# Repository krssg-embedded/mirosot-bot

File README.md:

# mirosot-bot
Board schematics, designs, layout. CAD files and relevant documentation regarding mirosot bots used in Code-O-Soccer Event

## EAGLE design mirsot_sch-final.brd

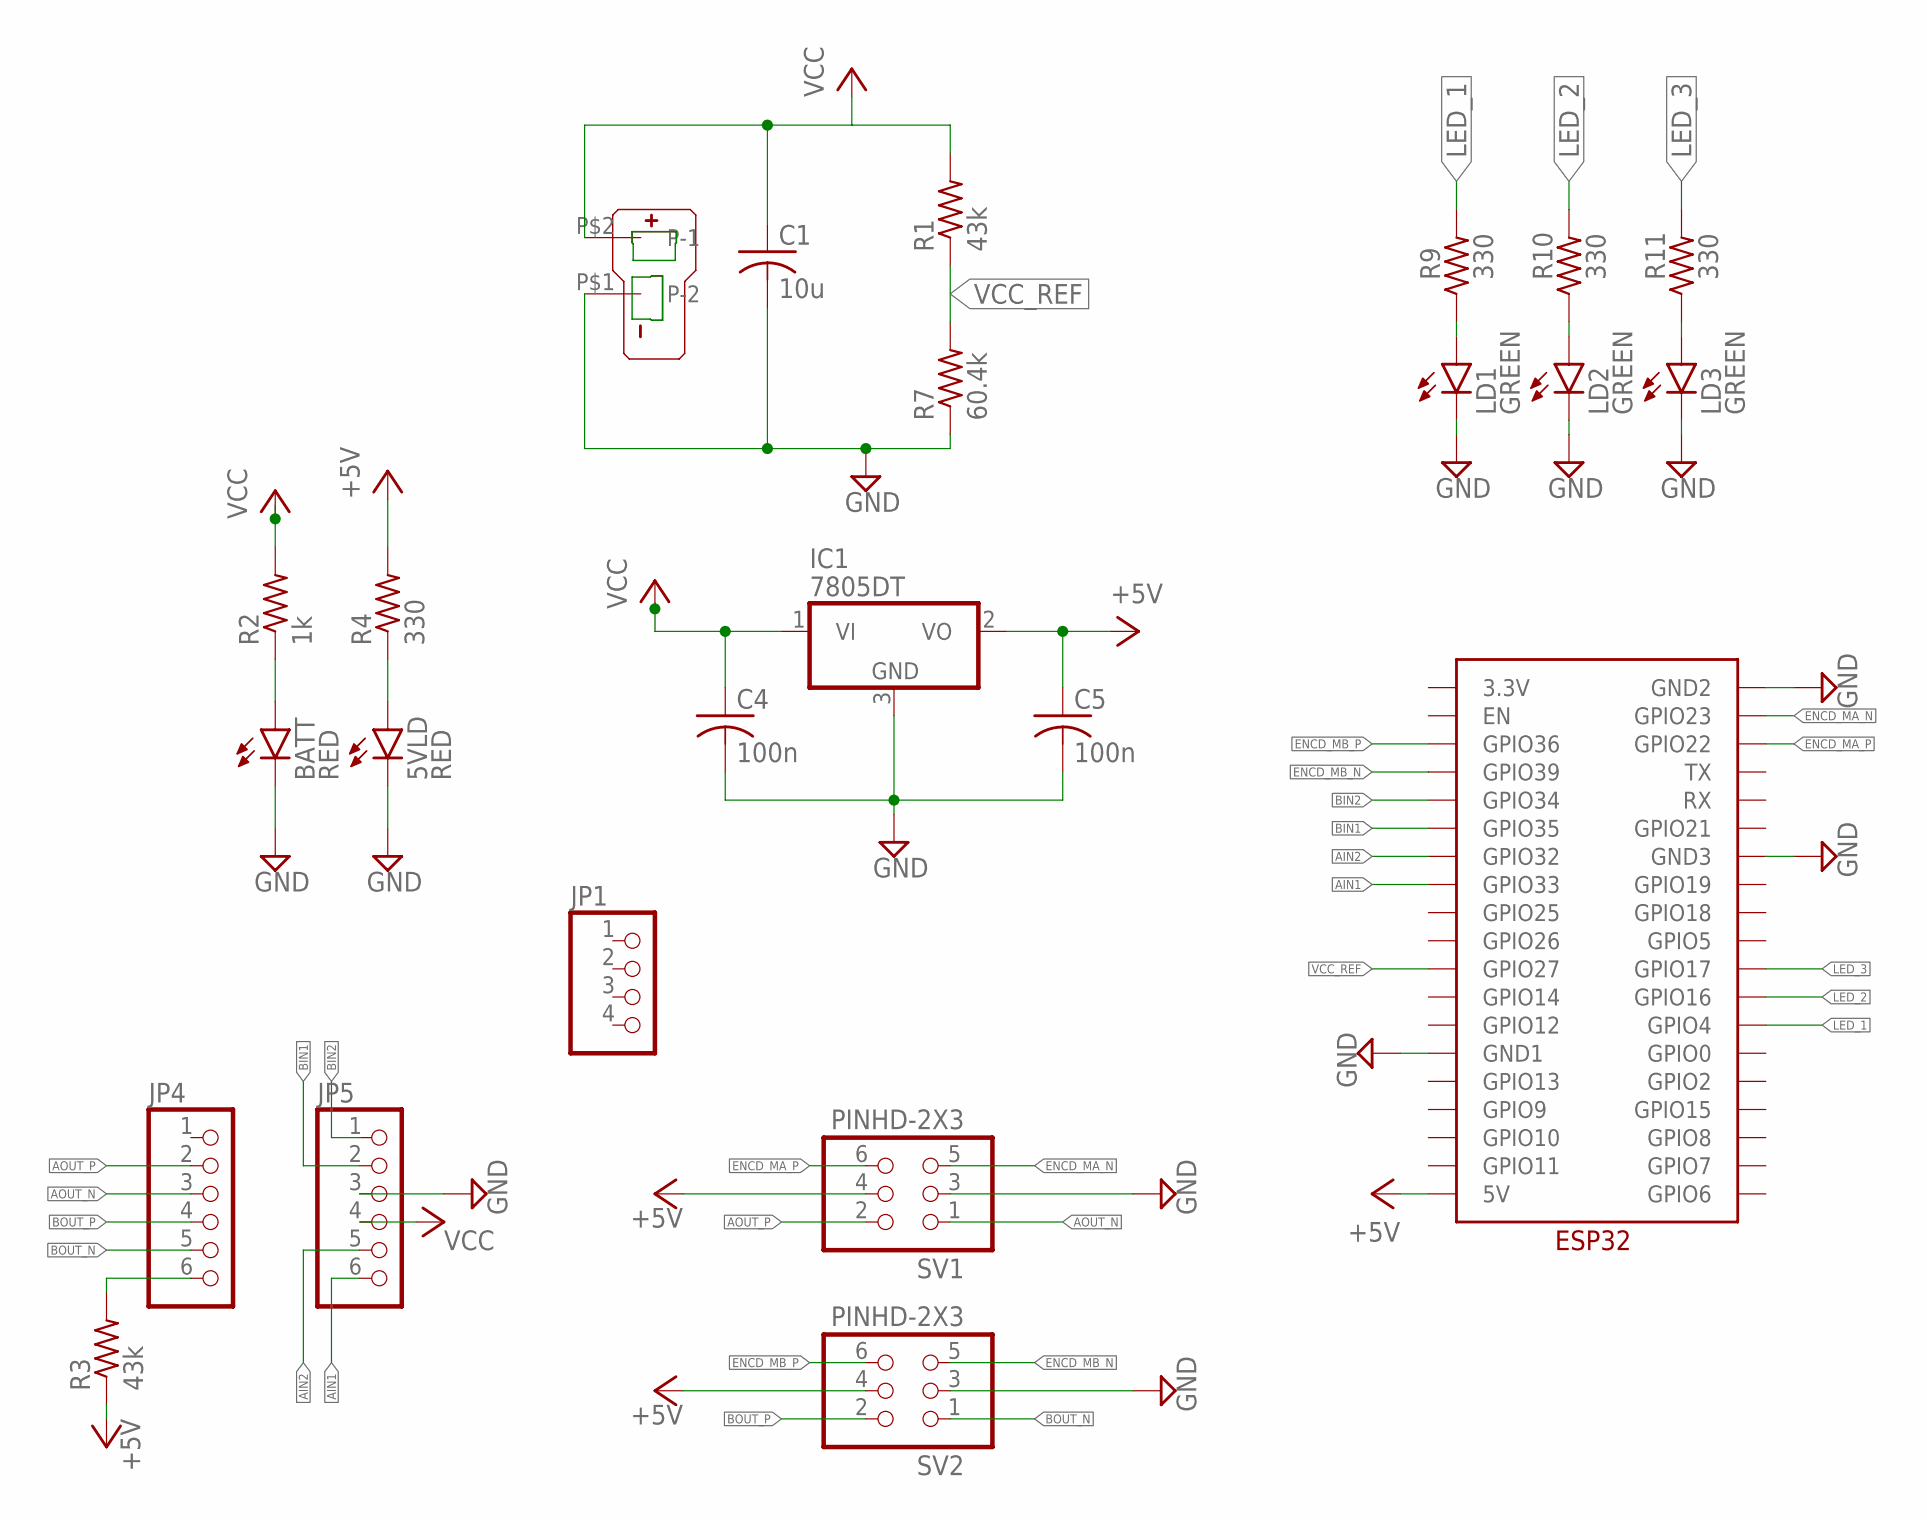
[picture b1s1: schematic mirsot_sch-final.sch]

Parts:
5VLD: RED; SML1206
BATT: RED; SML1206
C1: 10u; C1206K
C4, C5: 100n; C0603K
IC1: 7805DT; TO252
JP1: PINHD-1X4; 1X04
JP4, JP5: PINHD-1X6; 1X06
LD1, LD2, LD3: GREEN; SML1206
R1, R3: 43k; M1206
R2: 1k; M1206
R4, R9, R10, R11: 330; M1206
R7: 60.4k; M1206
SV1, SV2: PINHD-2X3; 2X03
U$1: T_PLUG_CONNECTOR_H
U$2: ESP32

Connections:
+5V: C5.1, IC1.2 (VO), R3.1, R4.2, SV1.4, SV2.4, U$2.5V
AIN1: JP5.6, U$2.GPIO33
AIN2: JP5.5, U$2.GPIO32
AOUT_N: JP4.3, SV1.1
AOUT_P: JP4.2, SV1.2
BIN1: JP5.2, U$2.GPIO35
BIN2: JP5.1, U$2.GPIO34
BOUT_N: JP4.5, SV2.1
BOUT_P: JP4.4, SV2.2
ENCD_MA_N: SV1.5, U$2.GPIO23
ENCD_MA_P: SV1.6, U$2.GPIO22
ENCD_MB_N: SV2.5, U$2.GPIO39
ENCD_MB_P: SV2.6, U$2.GPIO36
GND: 5VLD.C, BATT.C, C1.2, C4.2, C5.2, IC1.3 (GND), JP5.3, LD1.C, LD2.C, LD3.C, R7.1, SV1.3, SV2.3, U$1.P$1 (P-2), U$2.GND1, U$2.GND2, U$2.GND3
LED_1: R9.2, U$2.GPIO4
LED_2: R10.2, U$2.GPIO16
LED_3: R11.2, U$2.GPIO17
unnamed: JP4.6, R3.2
unnamed: BATT.A, R2.1
unnamed: LD1.A, R9.1
unnamed: LD2.A, R10.1
unnamed: 5VLD.A, R4.1
unnamed: LD3.A, R11.1
VCC: C1.1, C4.1, IC1.1 (VI), JP5.4, R1.2, R2.2, U$1.P$2 (P-1)
VCC_REF: R1.1, R7.2, U$2.GPIO27

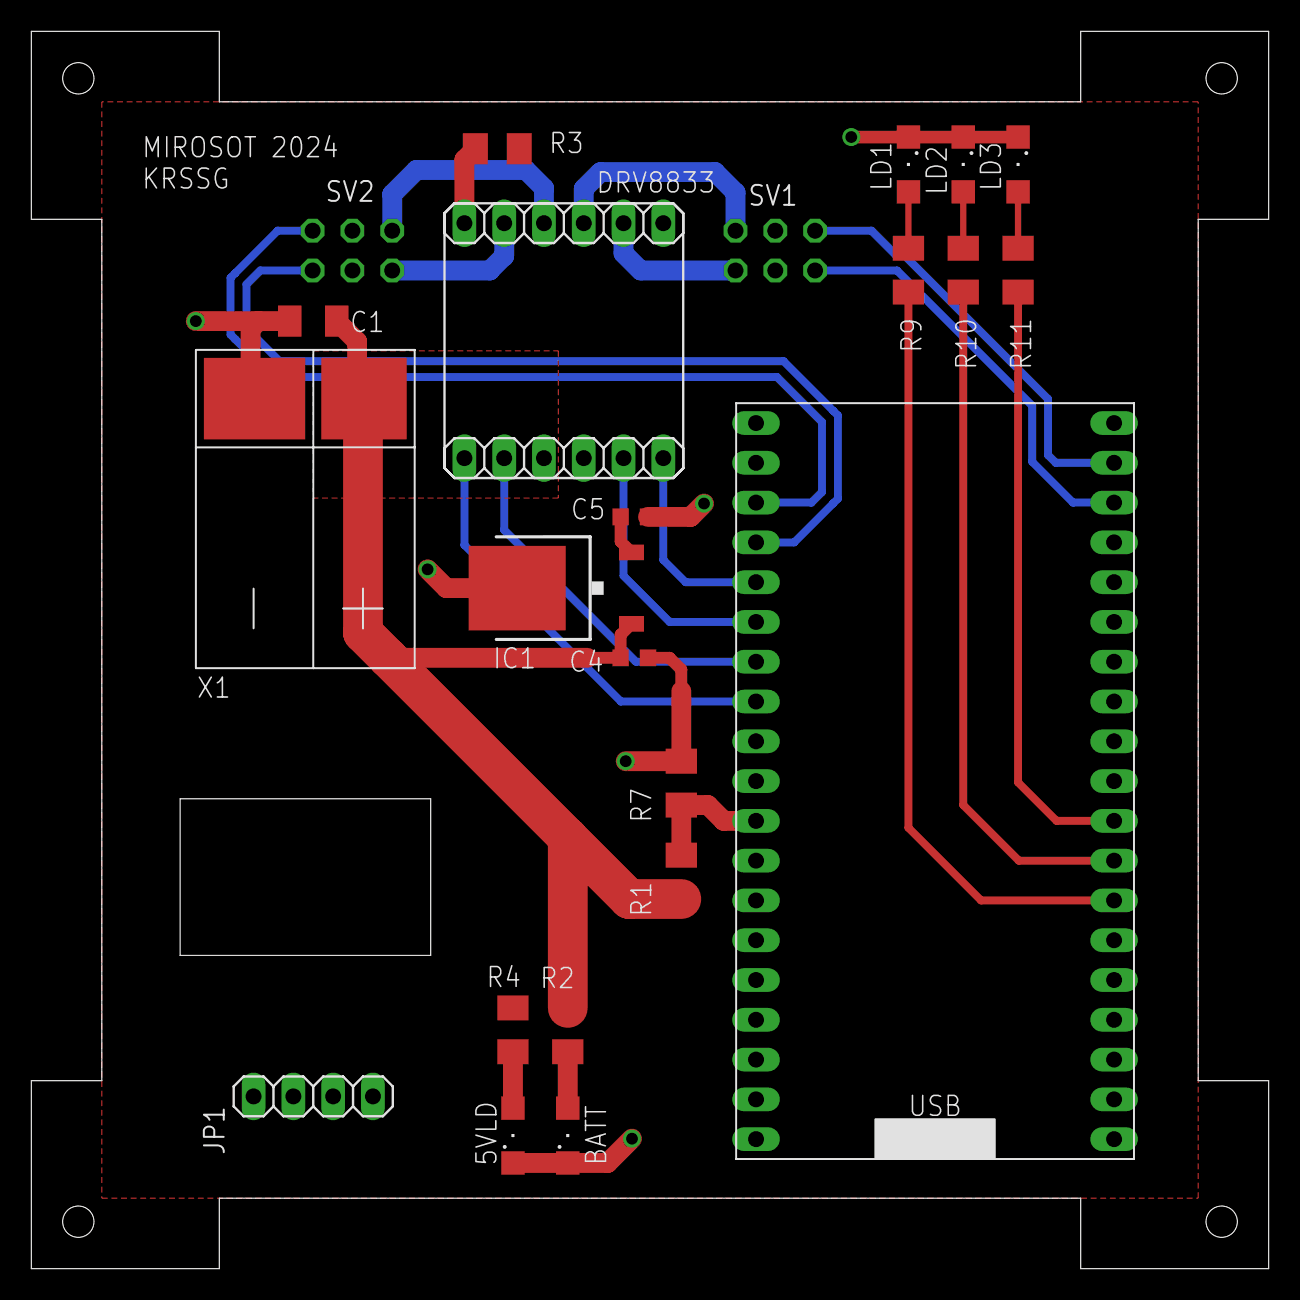
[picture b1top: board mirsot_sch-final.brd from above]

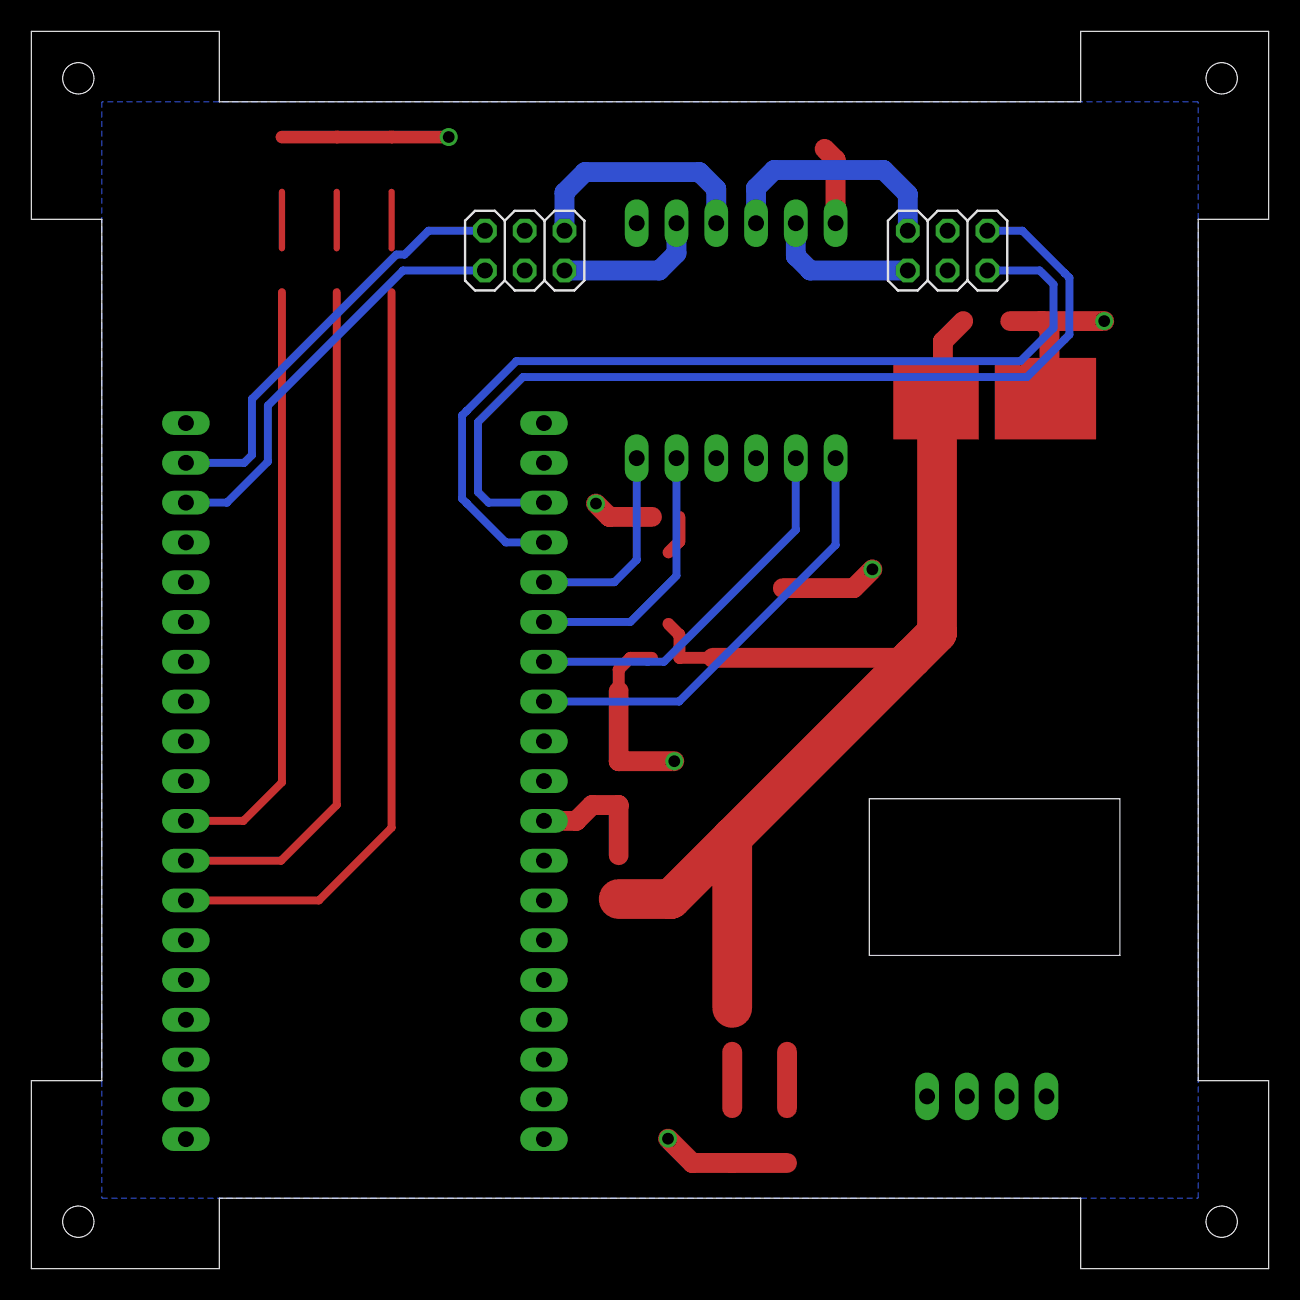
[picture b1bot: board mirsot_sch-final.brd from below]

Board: 2 copper layers, 79.0 x 79.0 mm, 24 parts (2 on the bottom side), 25 nets.

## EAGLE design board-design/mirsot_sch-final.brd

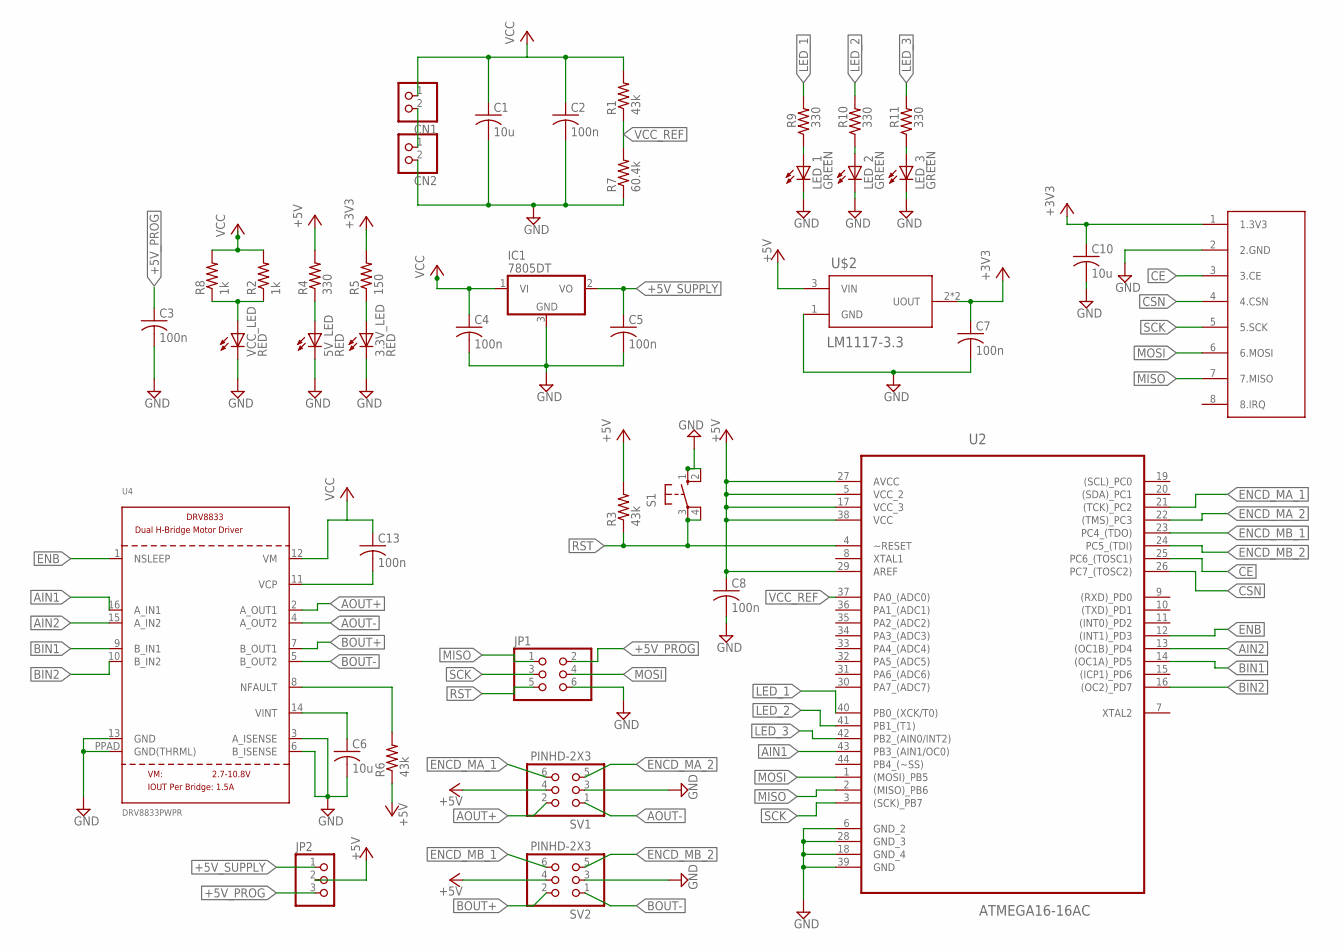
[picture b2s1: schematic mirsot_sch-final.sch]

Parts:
3.3V_LED, 5V_LED: RED; CHIPLED_0603
C1, C6, C10: 10u; C0603
C2, C3, C4, C5, C7, C8, C13: 100n; C0603
CN1, CN2: JST_2PIN-THM; JST-PH-2-THM
IC1: 7805DT; TO252
JP1: PINHD-2X3; 2X03
JP2: PINHD-1X3; 1X03
LED_1, LED_2, LED_3: GREEN; CHIPLED_0603
R1, R3, R6: 43k; R1206
R2, R8: 1k; R1206
R4, R9, R10, R11: 330; R1206
R5: 150; R2512
R7: 60.4k; R1206
S1: 10-XX; B3F-10XX
SV1, SV2: PINHD-2X3; 2X03
U2: ATMEGA16-16AC; QFP80P1200X1200X120-44N
U4: DRV8833PWPR; HTSSOP16
U$1: NRF24L01+
U$2: LM1117-3.3; SOT-223
VCC_LED: RED; CHIPLED_0603

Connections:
+3V3: C7.1, C10.1, R5.2, U$1.1 (1.3V3), U$2.2 (UOUT), U$2.4 (UOUT)
+5V: C8.1, JP2.2, R3.2, R4.2, R6.1, SV1.4, SV2.4, U2.5 (VCC_2), U2.17 (VCC_3), U2.27 (AVCC), U2.29 (AREF), U2.38 (VCC), U$2.3 (VIN)
+5V_PROG: C3.1, JP1.2, JP2.3
+5V_SUPPLY: C5.1, IC1.2 (VO), JP2.1
AIN1: U2.43 (PB3_(AIN1/OC0)), U4.16 (A_IN1)
AIN2: U2.13 ((OC1B)_PD4), U4.15 (A_IN2)
AOUT+: SV1.2, U4.2 (A_OUT1)
AOUT-: SV1.1, U4.4 (A_OUT2)
BIN1: U2.14 ((OC1A)_PD5), U4.9 (B_IN1)
BIN2: U2.16 ((OC2)_PD7), U4.10 (B_IN2)
BOUT+: SV2.2, U4.7 (B_OUT1)
BOUT-: SV2.1, U4.5 (B_OUT2)
CE: U2.25 (PC6_(TOSC1)), U$1.3 (3.CE)
CSN: U2.26 (PC7_(TOSC2)), U$1.4 (4.CSN)
ENB: U2.12 ((INT1)_PD3), U4.1 (NSLEEP)
ENCD_MA_1: SV1.6, U2.21 ((TCK)_PC2)
ENCD_MA_2: SV1.5, U2.22 ((TMS)_PC3)
ENCD_MB_1: SV2.6, U2.23 (PC4_(TDO))
ENCD_MB_2: SV2.5, U2.24 (PC5_(TDI))
GND: 3.3V_LED.C, 5V_LED.C, C1.2, C2.2, C3.2, C4.2, C5.2, C6.2, C7.2, C8.2, C10.2, CN2.2 (1), IC1.3 (GND), JP1.6, LED_1.C, LED_2.C, LED_3.C, R7.1, S1.1 (S), S1.2 (S1), SV1.3, SV2.3, U2.6 (GND_2), U2.18 (GND_4), U2.28 (GND_3), U2.39 (GND), U4.3 (A_ISENSE), U4.6 (B_ISENSE), U4.13 (GND), U4.PPAD (GND(THRML)), U$1.2 (2.GND), U$2.1 (GND), VCC_LED.C
LED_1: R9.2, U2.40 (PB0_(XCK/T0))
LED_2: R10.2, U2.41 (PB1_(T1))
LED_3: R11.2, U2.42 (PB2_(AIN0/INT2))
MISO: JP1.1, U2.2 ((MISO)_PB6), U$1.7 (7.MISO)
MOSI: JP1.4, U2.1 ((MOSI)_PB5), U$1.6 (6.MOSI)
unnamed: CN1.2 (1), CN2.1 (2)
unnamed: R2.1, R8.1, VCC_LED.A
unnamed: LED_1.A, R9.1
unnamed: LED_2.A, R10.1
unnamed: 5V_LED.A, R4.1
unnamed: 3.3V_LED.A, R5.1
unnamed: C13.2, U4.11 (VCP)
unnamed: C6.1, U4.14 (VINT)
unnamed: LED_3.A, R11.1
NFAULT: R6.2, U4.8 (NFAULT)
RST: JP1.5, R3.1, S1.3, S1.4 (P1), U2.4 (~RESET)
SCK: JP1.3, U2.3 ((SCK)_PB7), U$1.5 (5.SCK)
VCC: C1.1, C2.1, C4.1, C13.1, CN1.1 (2), IC1.1 (VI), R1.2, R2.2, R8.2, U4.12 (VM)
VCC_REF: R1.1, R7.2, U2.37 (PA0_(ADC0))

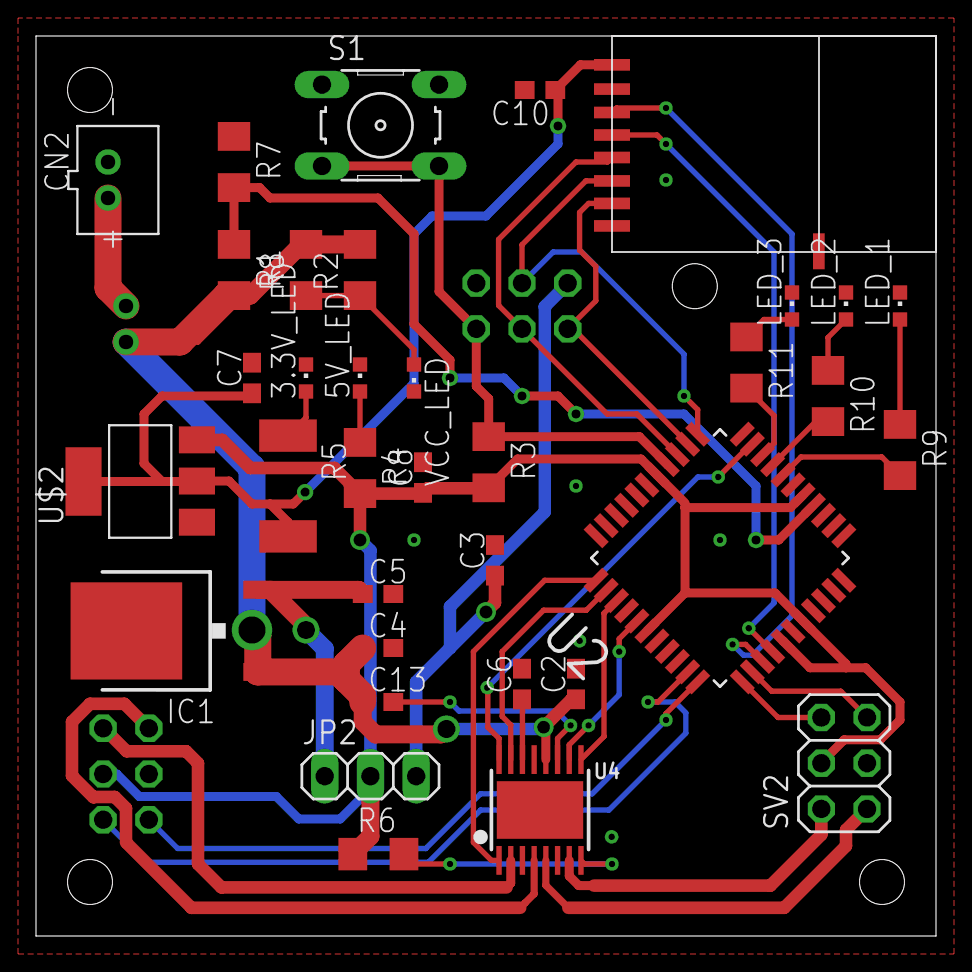
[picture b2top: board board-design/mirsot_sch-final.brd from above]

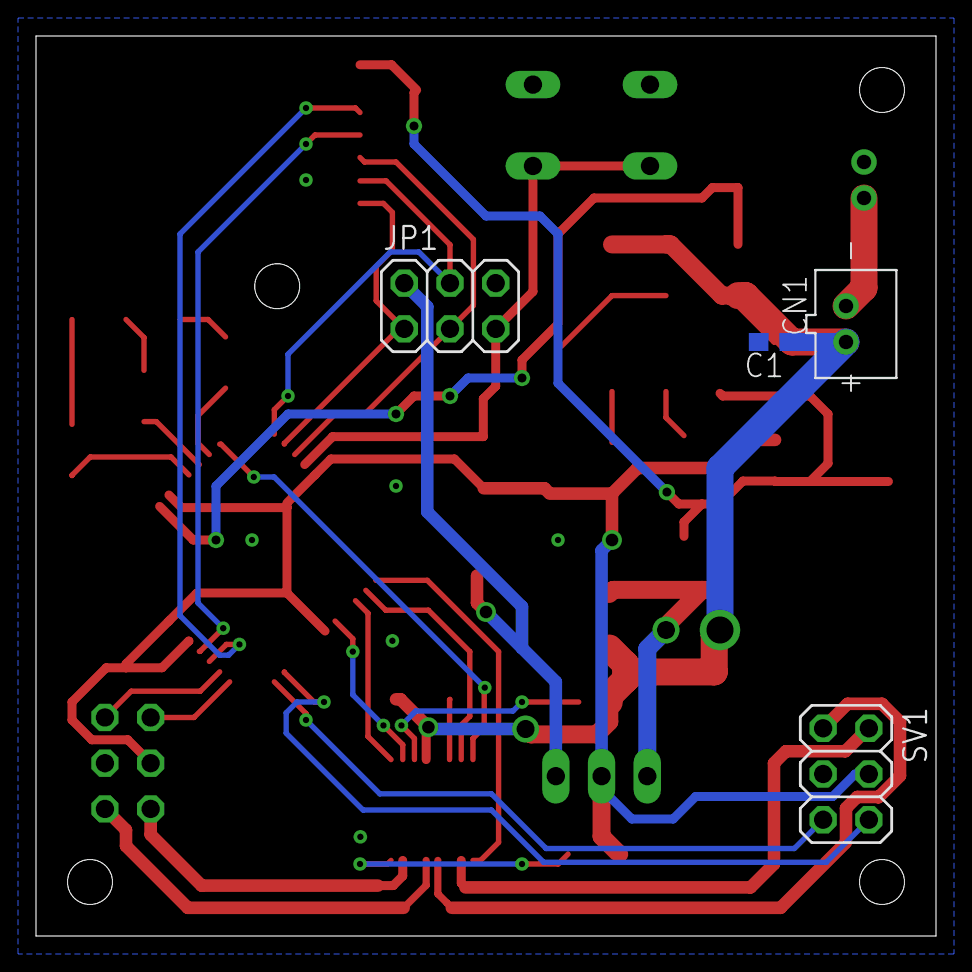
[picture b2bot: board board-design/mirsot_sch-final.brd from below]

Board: 2 copper layers, 50.0 x 50.0 mm, 39 parts (4 on the bottom side), 39 nets.

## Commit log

2023-10-08 Added schematic and board files
2023-10-10 Revert "Added schematic and board files"
    This reverts commit b98a6ca77ea148d8681f60614f8ed860d90c8fe2.
2023-10-10 Mirosot Schematic and Board Layout
2023-10-16 shifted from smd to tht
2023-10-16 added drv8833 module
2023-10-17 Routing Done
2023-10-30 board changed
2023-11-03 shifted NRF module
2023-11-04 finalized pcb
2023-11-11 changed battery connecter orientation
2023-11-15 changed mcu to esp32
2023-12-10 added level shifter, changed hole size, added switch
